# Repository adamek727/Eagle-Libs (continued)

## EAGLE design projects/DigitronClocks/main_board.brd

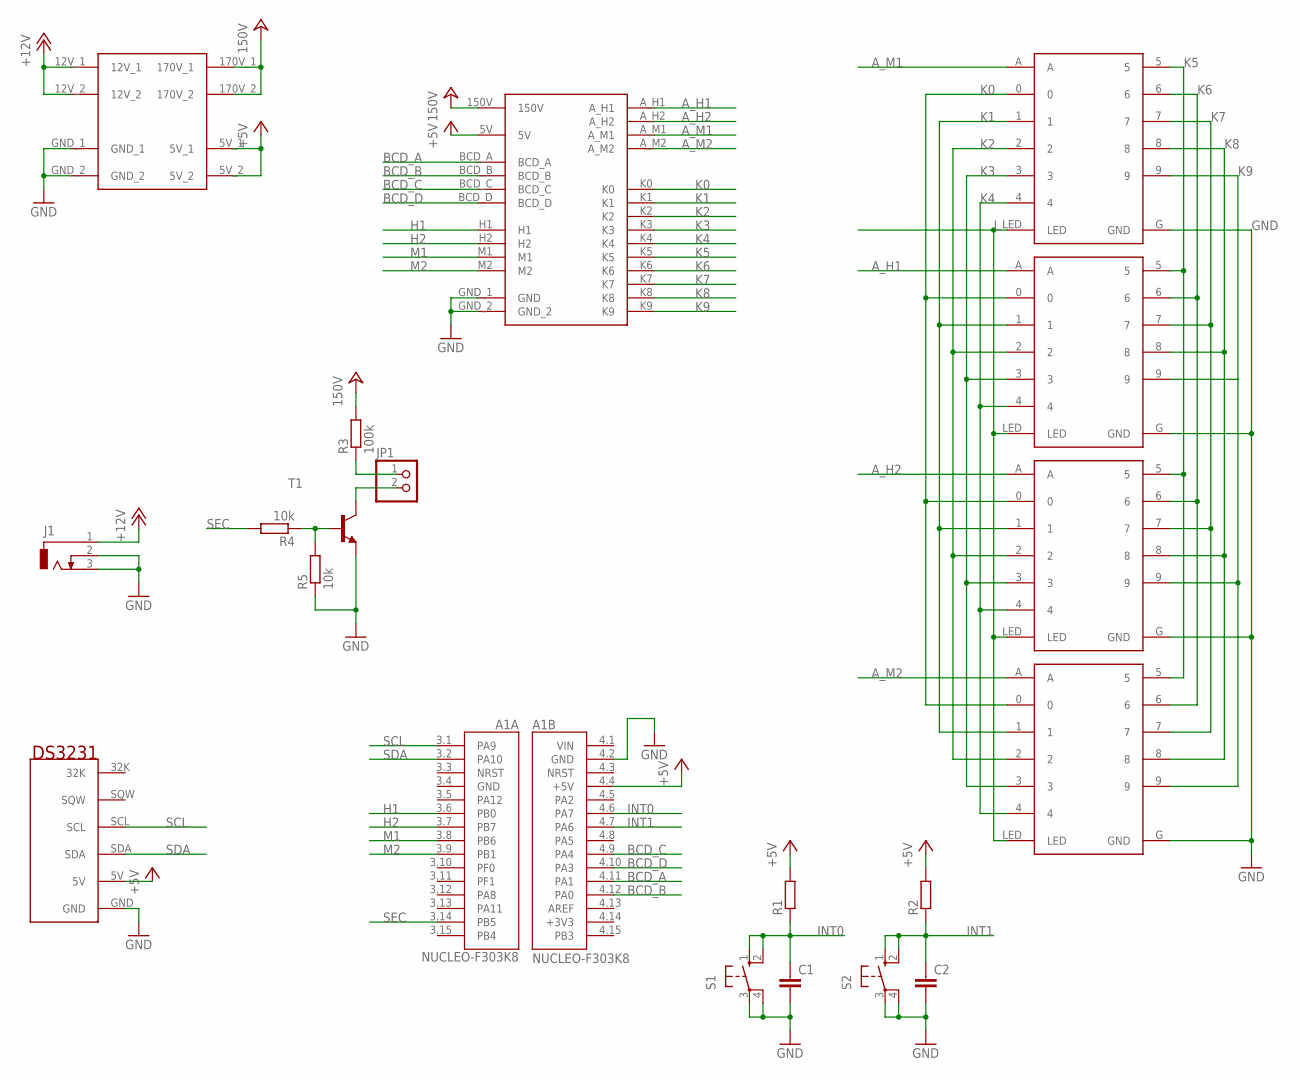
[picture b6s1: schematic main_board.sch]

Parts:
A1: NUCLEO-F303K8; MODULE_NUCLEO-F303K8
C1, C2: C-EUC1206; C1206
J1: DCJ0303
JP1: PINHD-1X2; 1X02
R1, R2: R-EU_R1206; R1206
R3: 100k; R1206
R4, R5: 10k; R1206
S1, S2: 10-XX; B3F-10XX
T1: MMBTA42LT1-NPN-SOT23-BEC; SOT23-BEC
U$1, U$2, U$3, U$4: Z570M_MODULE
U$5: POWER_MOUDLE; POWER_MODULE
U$6: RTC_MODULE
U$7: MATRIX_MODULE

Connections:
+5V: A1.4.4 (+5V), R1.2, R2.2, U$5.5V_1, U$5.5V_2, U$6.5V, U$7.5V
+12V: J1.1, U$5.12V_1, U$5.12V_2
+24V: R3.2, U$5.170V_1, U$5.170V_2, U$7.150V
A_H1: U$4.A, U$7.A_H1
A_H2: U$3.A, U$7.A_H2
A_M1: U$1.A, U$7.A_M1
A_M2: U$2.A, U$7.A_M2
BCD_A: A1.4.11 (PA1), U$7.BCD_A
BCD_B: A1.4.12 (PA0), U$7.BCD_B
BCD_C: A1.4.9 (PA4), U$7.BCD_C
BCD_D: A1.4.10 (PA3), U$7.BCD_D
GND: A1.4.2 (GND), C1.2, C2.2, J1.2, J1.3, R5.1, S1.3, S1.4 (P1), S2.3, S2.4 (P1), T1.E, U$1.G (GND), U$2.G (GND), U$3.G (GND), U$4.G (GND), U$5.GND_1, U$5.GND_2, U$6.GND, U$7.GND_1 (GND), U$7.GND_2
H1: A1.3.6 (PB0), U$7.H1
H2: A1.3.7 (PB7), U$7.H2
INT0: A1.4.6 (PA7), C1.1, R1.1, S1.1 (S), S1.2 (S1)
INT1: A1.4.7 (PA6), C2.1, R2.1, S2.1 (S), S2.2 (S1)
K0: U$1.0, U$2.0, U$3.0, U$4.0, U$7.K0
K1: U$1.1, U$2.1, U$3.1, U$4.1, U$7.K1
K2: U$1.2, U$2.2, U$3.2, U$4.2, U$7.K2
K3: U$1.3, U$2.3, U$3.3, U$4.3, U$7.K3
K4: U$1.4, U$2.4, U$3.4, U$4.4, U$7.K4
K5: U$1.5, U$2.5, U$3.5, U$4.5, U$7.K5
K6: U$1.6, U$2.6, U$3.6, U$4.6, U$7.K6
K7: U$1.7, U$2.7, U$3.7, U$4.7, U$7.K7
K8: U$1.8, U$2.8, U$3.8, U$4.8, U$7.K8
K9: U$1.9, U$2.9, U$3.9, U$4.9, U$7.K9
L: U$1.LED, U$2.LED, U$3.LED, U$4.LED
M1: A1.3.8 (PB6), U$7.M1
M2: A1.3.9 (PB1), U$7.M2
unnamed: JP1.1, R3.1
unnamed: JP1.2, T1.C
unnamed: R4.1, R5.2, T1.B
SCL: A1.3.1 (PA9), U$6.SCL
SDA: A1.3.2 (PA10), U$6.SDA
SEC: A1.3.14 (PB5), R4.2

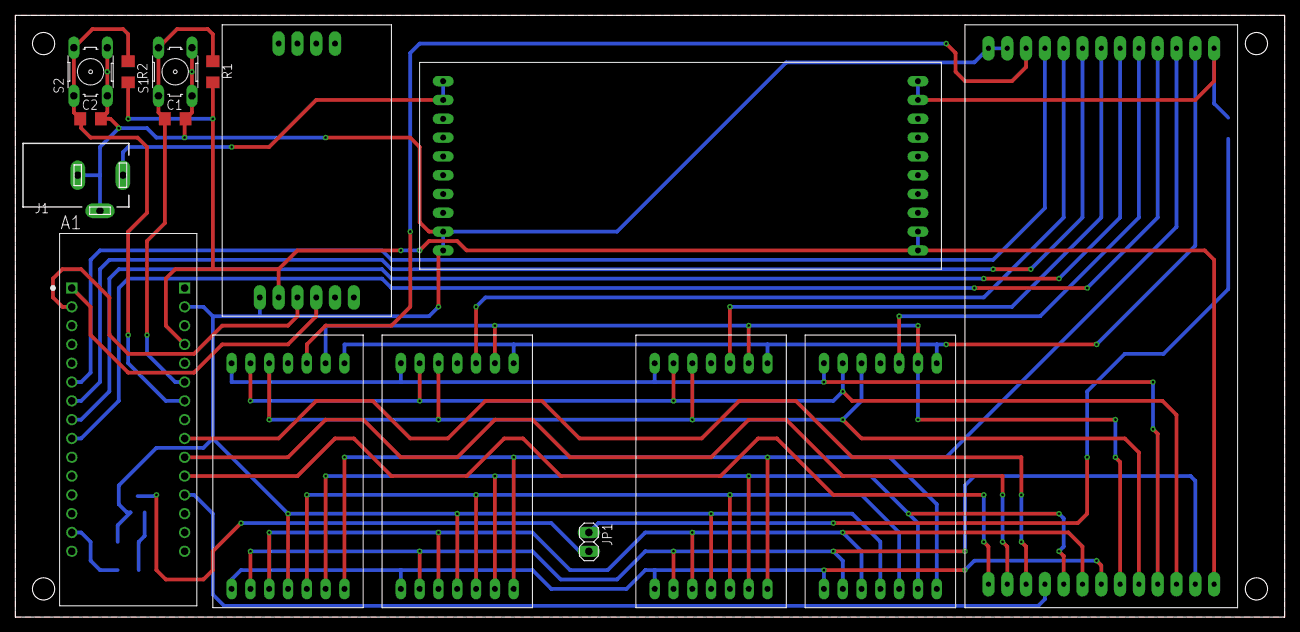
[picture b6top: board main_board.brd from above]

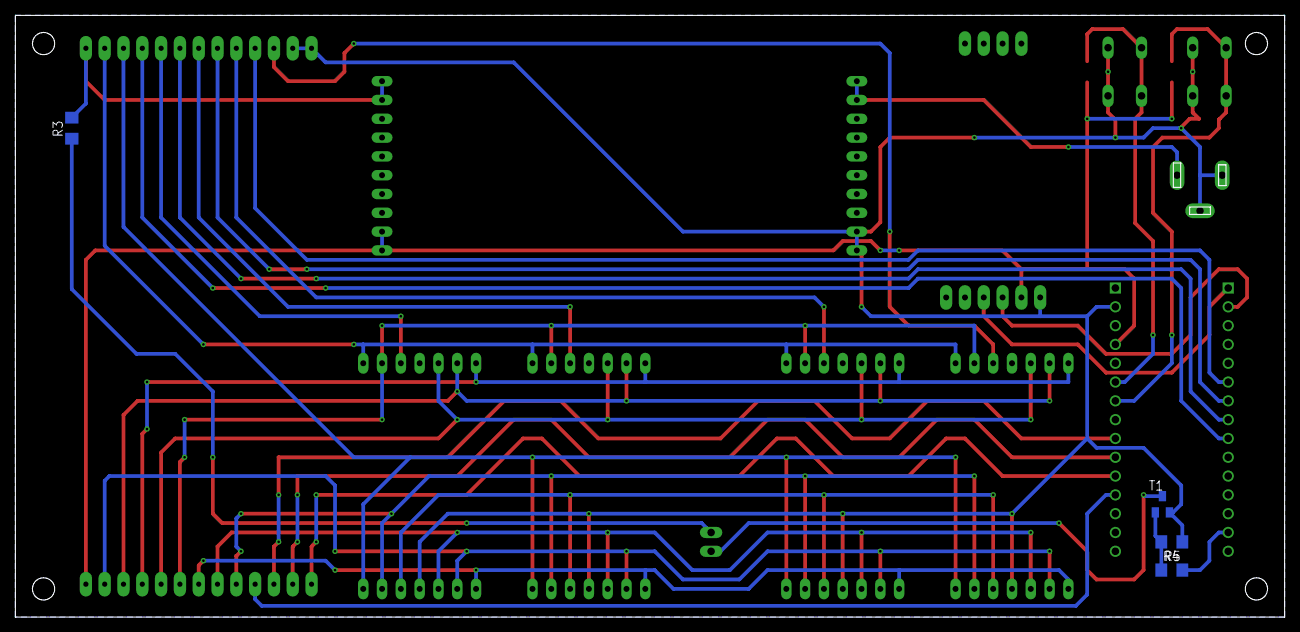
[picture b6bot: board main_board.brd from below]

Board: 2 copper layers, 171.4 x 81.3 mm, 20 parts (4 on the bottom side), 35 nets.
